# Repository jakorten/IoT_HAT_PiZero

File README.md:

# IoT HAT for Pi Zero

Leuk zo'n Raspberry Pi Zero van i&i, maar hoe doe je er nu IoT mee?!
- optie A: USB hub of zo, dan een Ethernet of WiFi dongle
- optie B: Weggooien en vervangen door een Raspberry Pi Zero W, maar ja zonde, gemiste kans!
- optie C: Gewoon een IoT HAT er op plaatsen!

LoRa, ZigBee, WiFi, Bluetooth Low Energy?
Eigenlijk wilde ik het zo universeel mogelijk maken, door er een XBee header op te plaatsen kun je gewoon kiezen welke module je wilt gebruiken.

N.b. Deze HAT werd geïnspireerd door: https://sixfab.com/product/xbee-shield/ welke is al meer uit ontwikkeld / te koop is.

### Over die HAT
Die originele HAT is in feite een https://www.sparkfun.com/products/11812 maar dan in HAT vorm.
Dat is mooi, maar ik heb gewoon een voorraad van die XBee Explorers liggen en wil er toch geen échte XBee's mee programmeren.

### Mijn versie:
- Het idee van direct met USB verbinden met de XBee module leek me echter wel een goed idee dus ik heb de selectie Pi/USB wel aangehouden.
- Er zit ook een NeoPixel LED op de HAT die je vanaf je Pi aan kunt sturen.
- Daarnaast een Vochtigheids/Temperatuur sensor via i2c én een i2c header voor evt andere sensor.
- Een flash geheugen chip want anders mag het geen HAT genoemd worden.

N.b. Dit is natuurlijk eerste versie dus ws. moet ik er nog aan sleutelen en het zal even duren voor ik de printjes van deze versie uit China binnen heb en gesoldeerd heb. Laat gerust weten als je interesse hebt. Dit is niet mijn eerste HAT die ik maak, ik heb o.a. weerstation HAT's, aansturingen voor tuinberegening, etc. daarnaast 'uiteraard' voor mijn reanimatie simulator.

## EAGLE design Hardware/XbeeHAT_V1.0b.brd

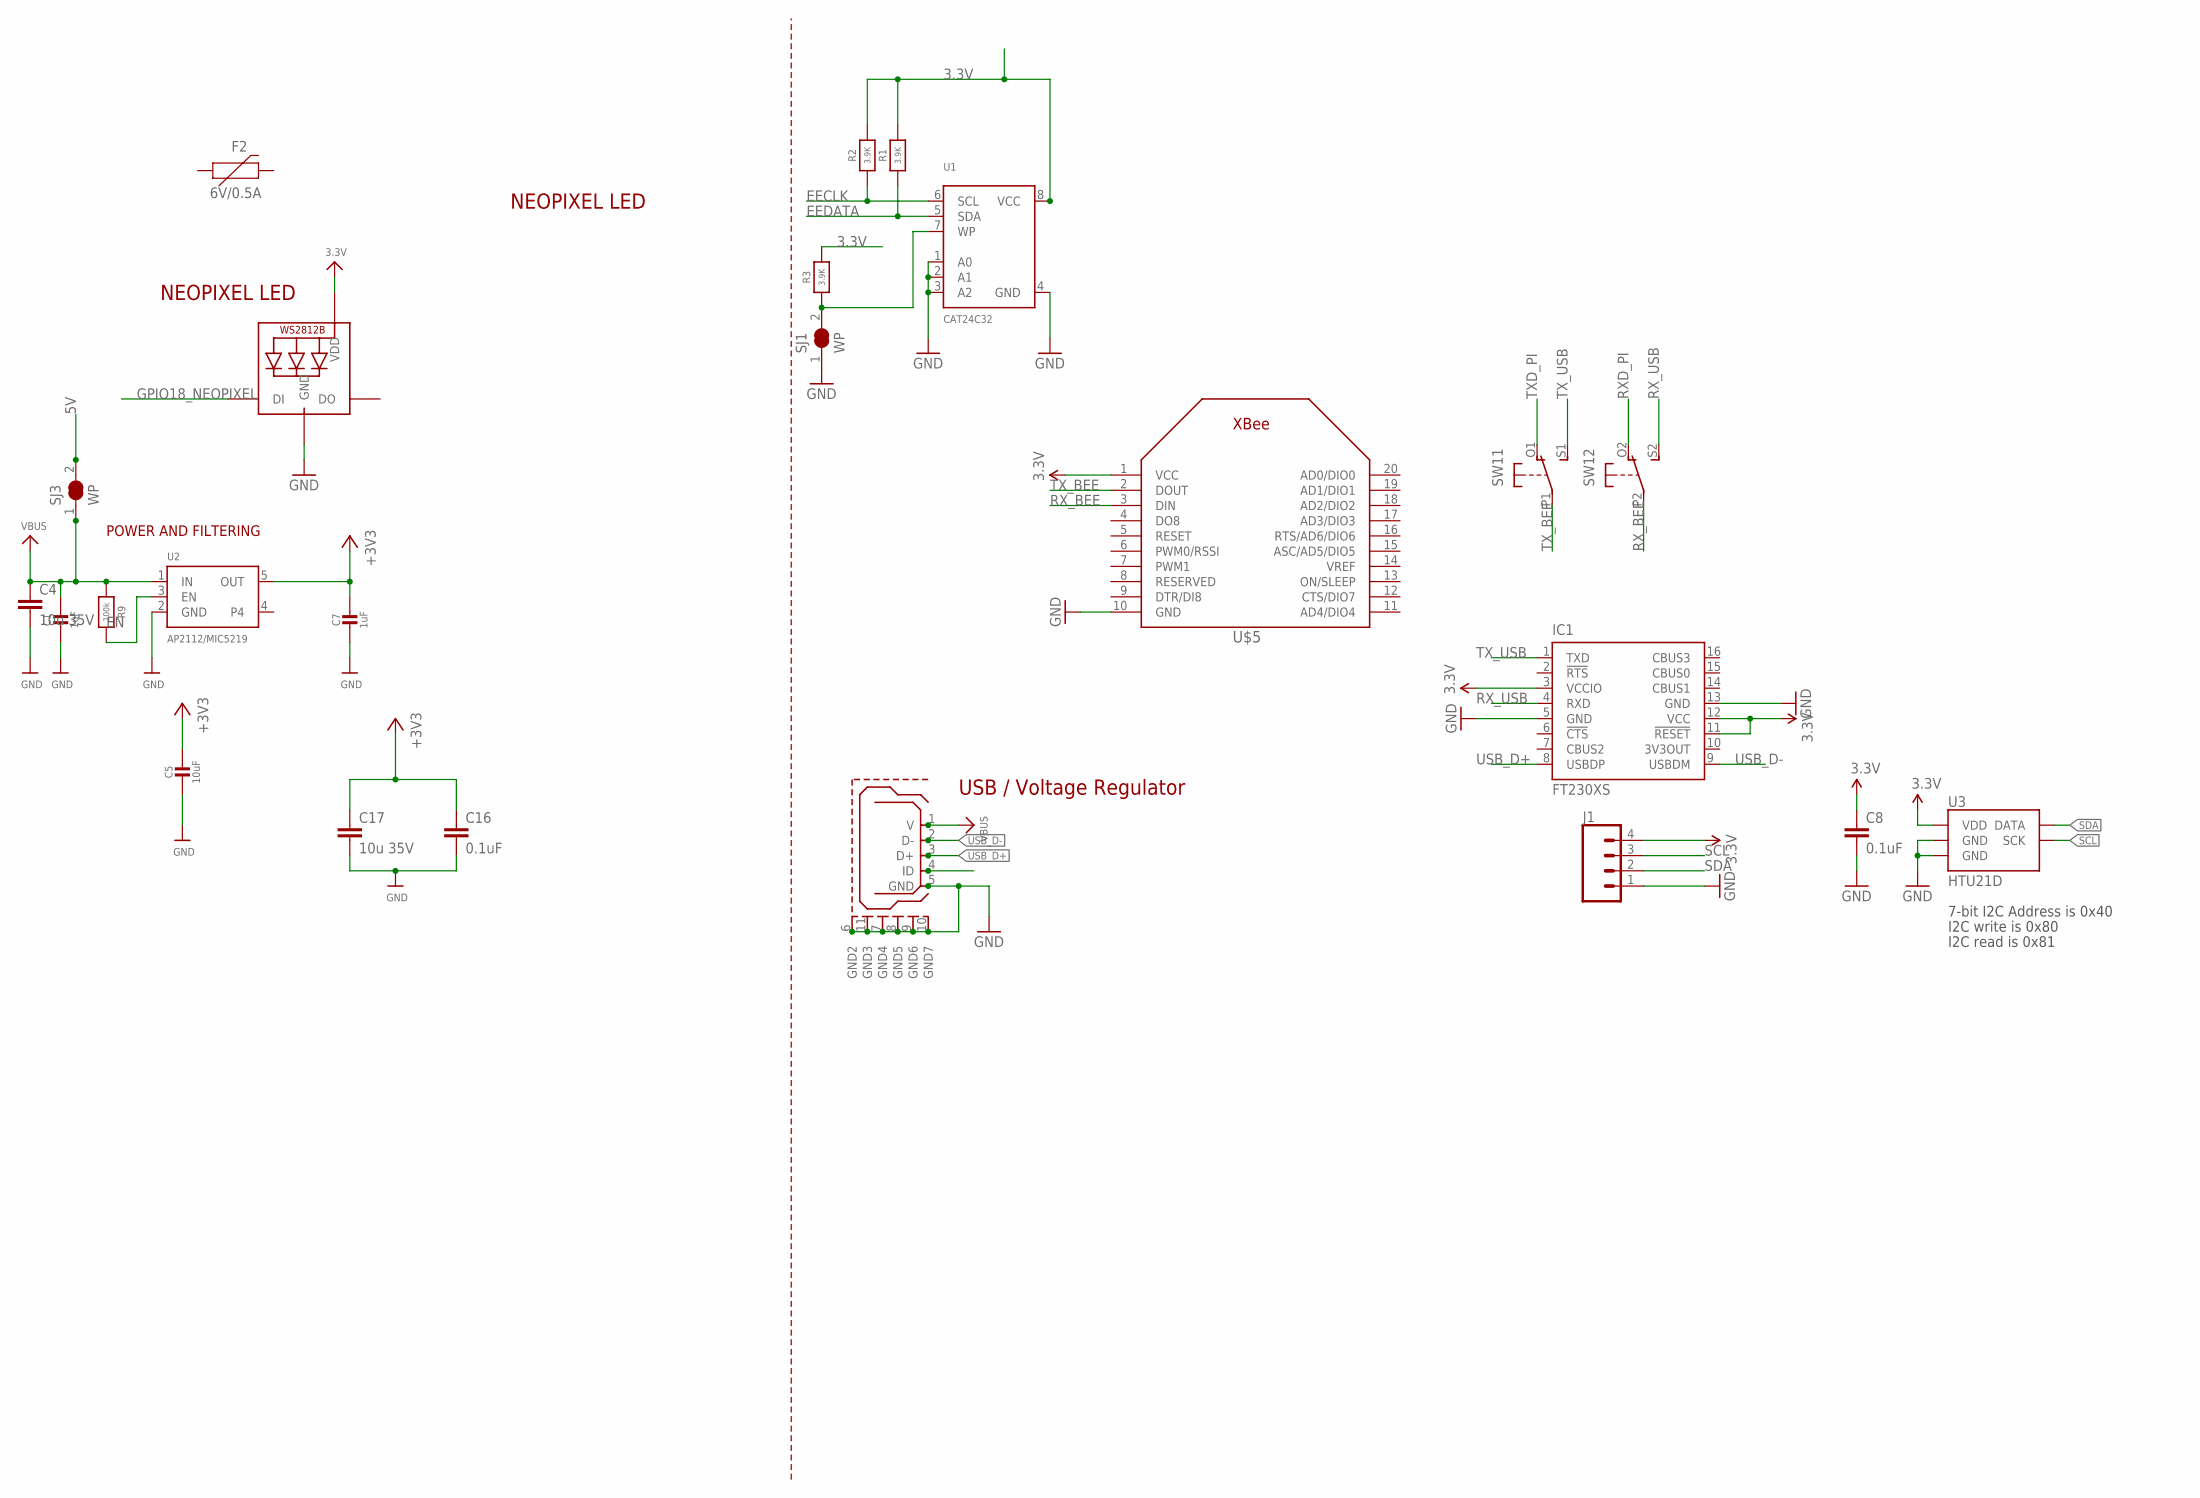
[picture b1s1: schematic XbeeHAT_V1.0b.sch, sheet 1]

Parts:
798-ZX62-B-5PA1: USB_MICROB; USB_MICROB_PACKAGE
C1, C7: 1uF; 0603-NO
C4, C17: 10u 35V; C1210
C5: 10uF; 0805-NO
C8: 0.1uF; 0603-CAP
C16: 0.1uF; C0805
F2: 6V/0.5A; 1206
IC1: FT230XS; SSOP16
J1: CONN_04; 1X04
LED: WS2812B3535; LED3535
R1, R2, R3: 3.9K; 0805-NO@1
R9: 100k; 0603-NO@1
SJ1, SJ3: WP; SOLDERJUMPER_CLOSEDWIRE
SW1: DPDT-EG1390; EG1390
U1: CAT24C32; SOIC8_150MIL
U2: AP2112/MIC5219; SOT23-5
U3: HTU21D
U$5: XBEE

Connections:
3.3V: C5.1, C7.1, C8.1, C16.1, C17.1, IC1.3 (VCCIO), IC1.11 (!RESET), IC1.12 (VCC), LED.2 (VDD), R1.2, R2.2, R3.2, U1.8 (VCC), U2.5 (OUT), U3.VDD, U$5.1 (VCC); also elsewhere on the board
5V: SJ3.2; also elsewhere on the board
EECLK: R2.1, U1.6 (SCL)
EEDATA: R1.1, U1.5 (SDA); also elsewhere on the board
EN: R9.2, U2.3 (EN)
GND: 798-ZX62-B-5PA1.5 (GND), 798-ZX62-B-5PA1.6 (GND2), 798-ZX62-B-5PA1.7 (GND4), 798-ZX62-B-5PA1.8 (GND5), 798-ZX62-B-5PA1.9 (GND6), 798-ZX62-B-5PA1.10 (GND7), 798-ZX62-B-5PA1.11 (GND3), C1.2, C4.2, C5.2, C7.2, C8.2, C16.2, C17.2, IC1.5 (GND), IC1.13 (GND), J1.1, LED.4 (GND), SJ1.1, U1.1 (A0), U1.2 (A1), U1.3 (A2), U1.4 (GND), U2.2 (GND), U3.7 (GND), U3.GND, U$5.10 (GND); also elsewhere on the board
GPIO18_NEOPIXEL: LED.1 (DI); also elsewhere on the board
unnamed: R3.1, SJ1.2, U1.7 (WP)
RXD_PI: SW1.O2 (O); also elsewhere on the board
RX_BEE: SW1.P2, U$5.3 (DIN)
RX_USB: IC1.4 (RXD), SW1.S2 (S)
SCL: J1.3, U3.SCK; also elsewhere on the board
SDA: J1.2, U3.DATA; also elsewhere on the board
TXD_PI: SW1.O1 (O); also elsewhere on the board
TX_BEE: SW1.P1, U$5.2 (DOUT)
TX_USB: IC1.1 (TXD), SW1.S1 (S)
USB_D+: 798-ZX62-B-5PA1.3 (D+), IC1.8 (USBDP)
USB_D-: 798-ZX62-B-5PA1.2 (D-), IC1.9 (USBDM)
VBUS: 798-ZX62-B-5PA1.1 (V), C1.1, C4.1, R9.1, SJ3.1, U2.1 (IN)
VCC: J1.4

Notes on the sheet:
POWER AND FILTERING
USB / Voltage Regulator
NEOPIXEL LED
7-bit I2C Address is 0x40
I2C write is 0x80
I2C read is 0x81

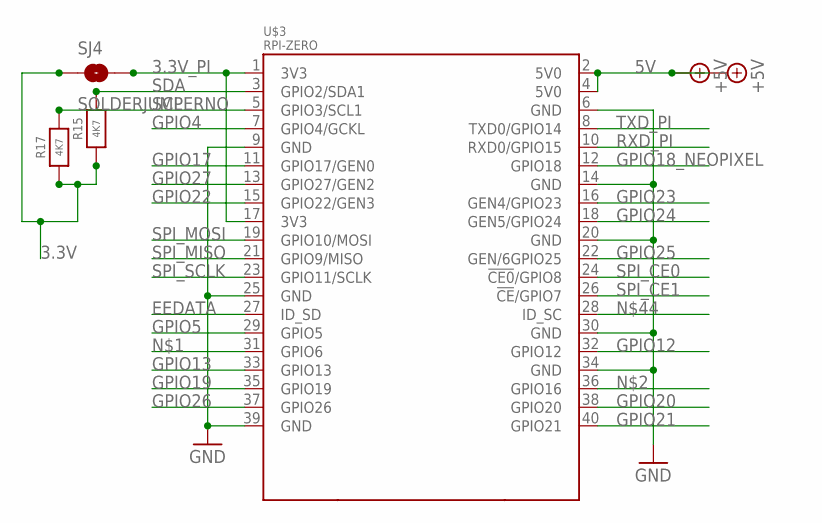
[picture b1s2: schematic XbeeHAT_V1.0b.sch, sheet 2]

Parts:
R15, R17: 4K7; 0805-NO@1
SJ4: SOLDERJUMPERNO; SJ_2S-NO
U$3: RPI-ZERO; RASPBERRYPI_BASTELSTUBE_V13_RASPI_BOARD_B+_FULL

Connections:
3.3V: R15.1, R17.1, SJ4.1; also elsewhere on the board
3.3V_PI: SJ4.2, U$3.1 (3V3), U$3.17 (3V3)
5V: U$3.2 (5V0), U$3.4 (5V0); also elsewhere on the board
EEDATA: U$3.27 (ID_SD); also elsewhere on the board
GND: U$3.6 (GND), U$3.9 (GND), U$3.14 (GND), U$3.20 (GND), U$3.25 (GND), U$3.30 (GND), U$3.34 (GND), U$3.39 (GND); also elsewhere on the board
GPIO4: U$3.7 (GPIO4/GCKL)
GPIO5: U$3.29 (GPIO5)
GPIO12: U$3.32 (GPIO12)
GPIO13: U$3.33 (GPIO13)
GPIO17: U$3.11 (GPIO17/GEN0)
GPIO18_NEOPIXEL: U$3.12 (GPIO18); also elsewhere on the board
GPIO19: U$3.35 (GPIO19)
GPIO20: U$3.38 (GPIO20)
GPIO21: U$3.40 (GPIO21)
GPIO22: U$3.15 (GPIO22/GEN3)
GPIO23: U$3.16 (GEN4/GPIO23)
GPIO24: U$3.18 (GEN5/GPIO24)
GPIO25: U$3.22 (GEN/6GPIO25)
GPIO26: U$3.37 (GPIO26)
GPIO27: U$3.13 (GPIO27/GEN2)
RXD_PI: U$3.10 (RXD0/GPIO15); also elsewhere on the board
SCL: R17.2, U$3.5 (GPIO3/SCL1); also elsewhere on the board
SDA: R15.2, U$3.3 (GPIO2/SDA1); also elsewhere on the board
SPI_CE0: U$3.24 (!CE0!/GPIO8)
SPI_CE1: U$3.26 (!CE!/GPIO7)
SPI_MISO: U$3.21 (GPIO9/MISO)
SPI_MOSI: U$3.19 (GPIO10/MOSI)
SPI_SCLK: U$3.23 (GPIO11/SCLK)
TXD_PI: U$3.8 (TXD0/GPIO14); also elsewhere on the board

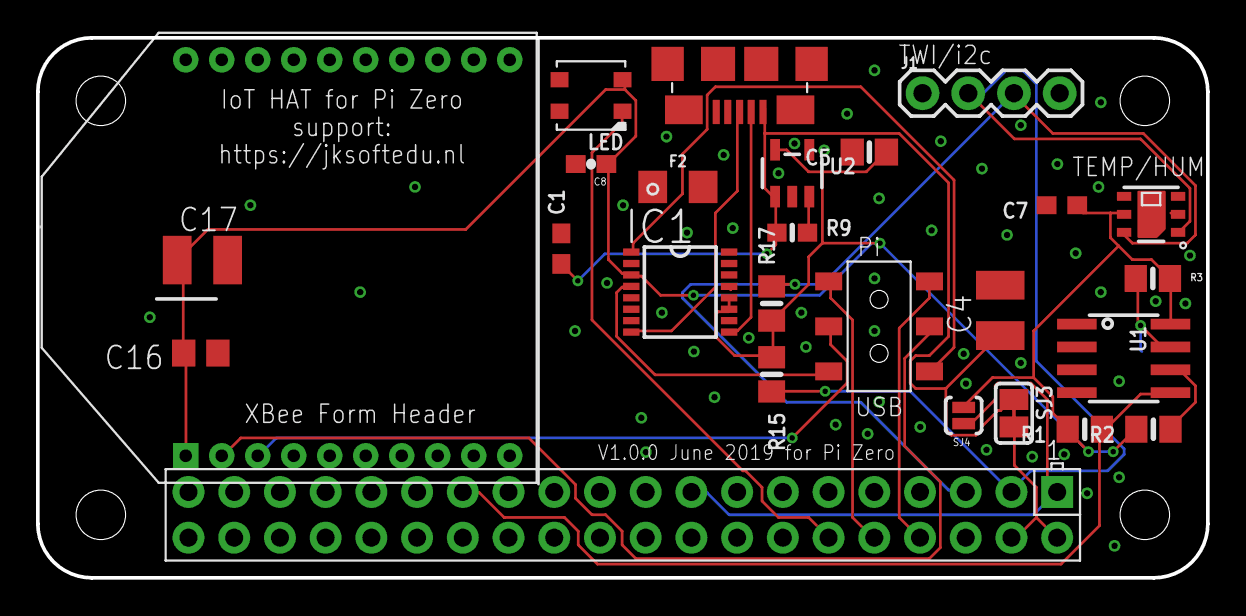
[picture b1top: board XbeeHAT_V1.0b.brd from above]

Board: 2 copper layers, 65.0 x 30.0 mm, 27 parts (1 on the bottom side), 20 nets.

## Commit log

2019-06-27 Hardware files
    Hardware files (eagle / gerber)
2019-06-27 Updated Images PCB
    Updated Images PCB

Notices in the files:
parts and their libraries:
microbuilder: This work is placed in the public domain, and may be freely used for commercial and non-commercial work with the following conditions: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
SparkFun-Capacitors: Licensing: CC v3.0 Share-Alike You are welcome to use this library for commercial purposes.
